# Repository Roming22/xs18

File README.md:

# xs18

18-key keyboard.

## Credits
- https://github.com/willpuckett/sessile-template

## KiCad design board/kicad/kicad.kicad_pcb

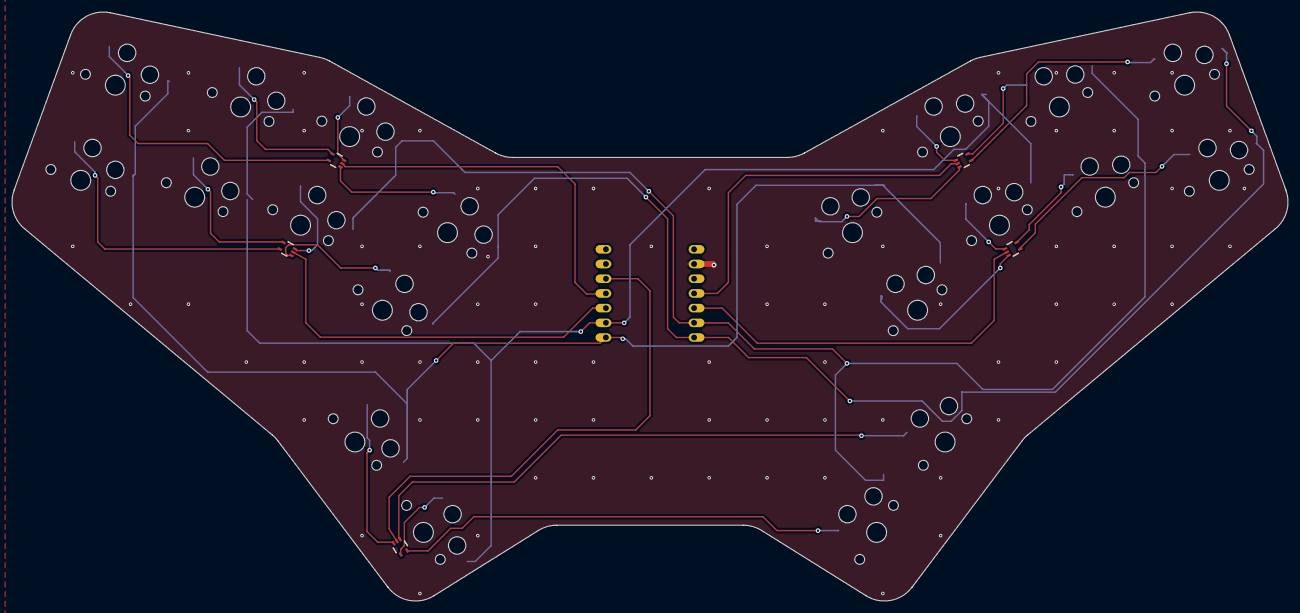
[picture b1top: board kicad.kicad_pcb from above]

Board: 2 copper layers, 220.5 x 101.8 mm, 26 parts (0 on the bottom side), 29 nets.

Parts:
D1, D2, D3, D4, D5: UMP1NTR; SOT-353_L2.1-W1.3-P0.65-LS2.3-BL
MCU1: xiao-ble
S1, S2, S3, S4, S5, S6, S7, S8, S9, S10, S11, S12, S13, S14, S15, S16, S17, S18, S19, S20: PG1350

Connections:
P0: MCU1.12, S1.2, S2.2, S15.2, S16.2, S17.2
P1: MCU1.7, S7.2, S8.2, S9.2, S10.2, S19.2
P2: MCU1.6, S5.2, S6.2, S11.2, S12.2, S20.2
P4: D3.2, MCU1.5
P5: D4.2, MCU1.4
P6: D1.2, MCU1.14
P7: MCU1.13, S3.2, S4.2, S13.2, S14.2, S18.2
P28: D5.2, MCU1.16
P29: D2.2, MCU1.15
home_default: D5.3, S17.1
index_home: D1.1, S7.1
index_top: D2.1, S8.1
middle_home: D1.3, S5.1
middle_top: D2.3, S6.1
mirror_home_default: D5.1, S19.1
mirror_index_home: D3.3, S15.1
mirror_index_top: D4.3, S16.1
mirror_middle_home: D3.1, S13.1
mirror_middle_top: D4.1, S14.1
mirror_outer_default: D5.5, S20.1
mirror_pinky_home: D3.4, S9.1
mirror_pinky_top: D4.4, S10.1
mirror_ring_home: D3.5, S11.1
mirror_ring_top: D4.5, S12.1
outer_default: D5.4, S18.1
pinky_home: D1.5, S1.1
pinky_top: D2.5, S2.1
ring_home: D1.4, S3.1
ring_top: D2.4, S4.1

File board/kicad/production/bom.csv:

Designator,Footprint,Quantity,Value,LCSC Part #
"D1, D2, D3, D4, D5",SOT-353_L2.1-W1.3-P0.65-LS2.3-BL,5,UMP1NTR,C510065
MCU1,xiao-ble,1,,
"S1, S10, S11, S12, S13, S14, S15, S16, S17, S18, S19, S2, S20, S3, S4, S5, S6, S7, S8, S9",PG1350,20,,

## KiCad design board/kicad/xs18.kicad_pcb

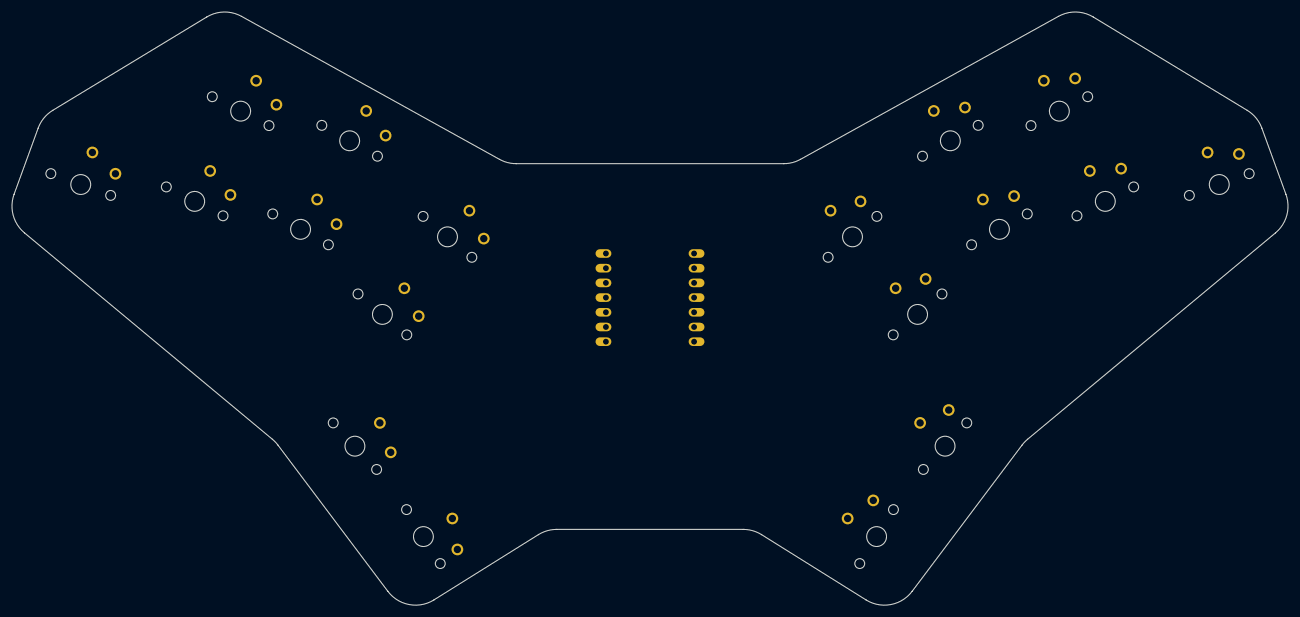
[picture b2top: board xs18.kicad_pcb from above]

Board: 2 copper layers, 220.5 x 102.5 mm, 19 parts (0 on the bottom side), 4 nets, no tracks yet.

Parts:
MCU1: xiao-ble
S1, S2, S3, S4, S5, S6, S7, S8, S9, S10, S11, S12, S13, S14, S15, S16, S17, S18: PG1350

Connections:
P0: MCU1.12, S1.2, S13.2, S14.2, S15.2
P1: MCU1.7, S6.2, S7.2, S8.2, S17.2
P2: MCU1.6, S4.2, S5.2, S9.2, S10.2, S18.2
P7: MCU1.13, S2.2, S3.2, S11.2, S12.2, S16.2

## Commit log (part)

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2025-04-21 chore: initial commit
2025-04-21 feat: ergogen tooling
2025-04-21 feat: add pinky key
2025-04-21 feat: add ring, middle, and index key
2025-04-21 feat: add top row
2025-04-21 feat: remove top pinky
2025-04-21 feat: add thumb cluster
2025-04-21 feat: add mirroring
2025-04-21 feat: add side angle
2025-04-21 feat: add vertical offset to ring, middle and index columns
2025-04-21 feat: add offsets to thumb cluster
2025-04-21 feat: add splay to all keys
2025-04-21 feat: fine tune key positions
2025-04-26 feat: pcb outline
2025-04-26 feat: add mcu
2025-05-10 feat: fine tune pcb outline
2025-05-10 feat: basic pcb generation
2025-05-25 feat: plan PCB routing
2025-05-25 feat: add xiao to PCB
2025-05-25 feat: add diodes to PCB
2025-05-26 feat: add hotswap sockets
2025-12-30 chore: update Dockerfile
    New dependencies are required to install the latest versions of the
    python modules.
2025-12-30 feat: 20 keys
2025-12-30 feat: add screws
2025-12-30 chore: upgrade kicad file version
    This is the result of opening the file generated by Ergogen in the
    latest kicad version.
